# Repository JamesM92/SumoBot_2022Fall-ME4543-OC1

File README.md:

# SumoBot_2022Fall-ME4543-OC1
group design project sumobot for mechatronics

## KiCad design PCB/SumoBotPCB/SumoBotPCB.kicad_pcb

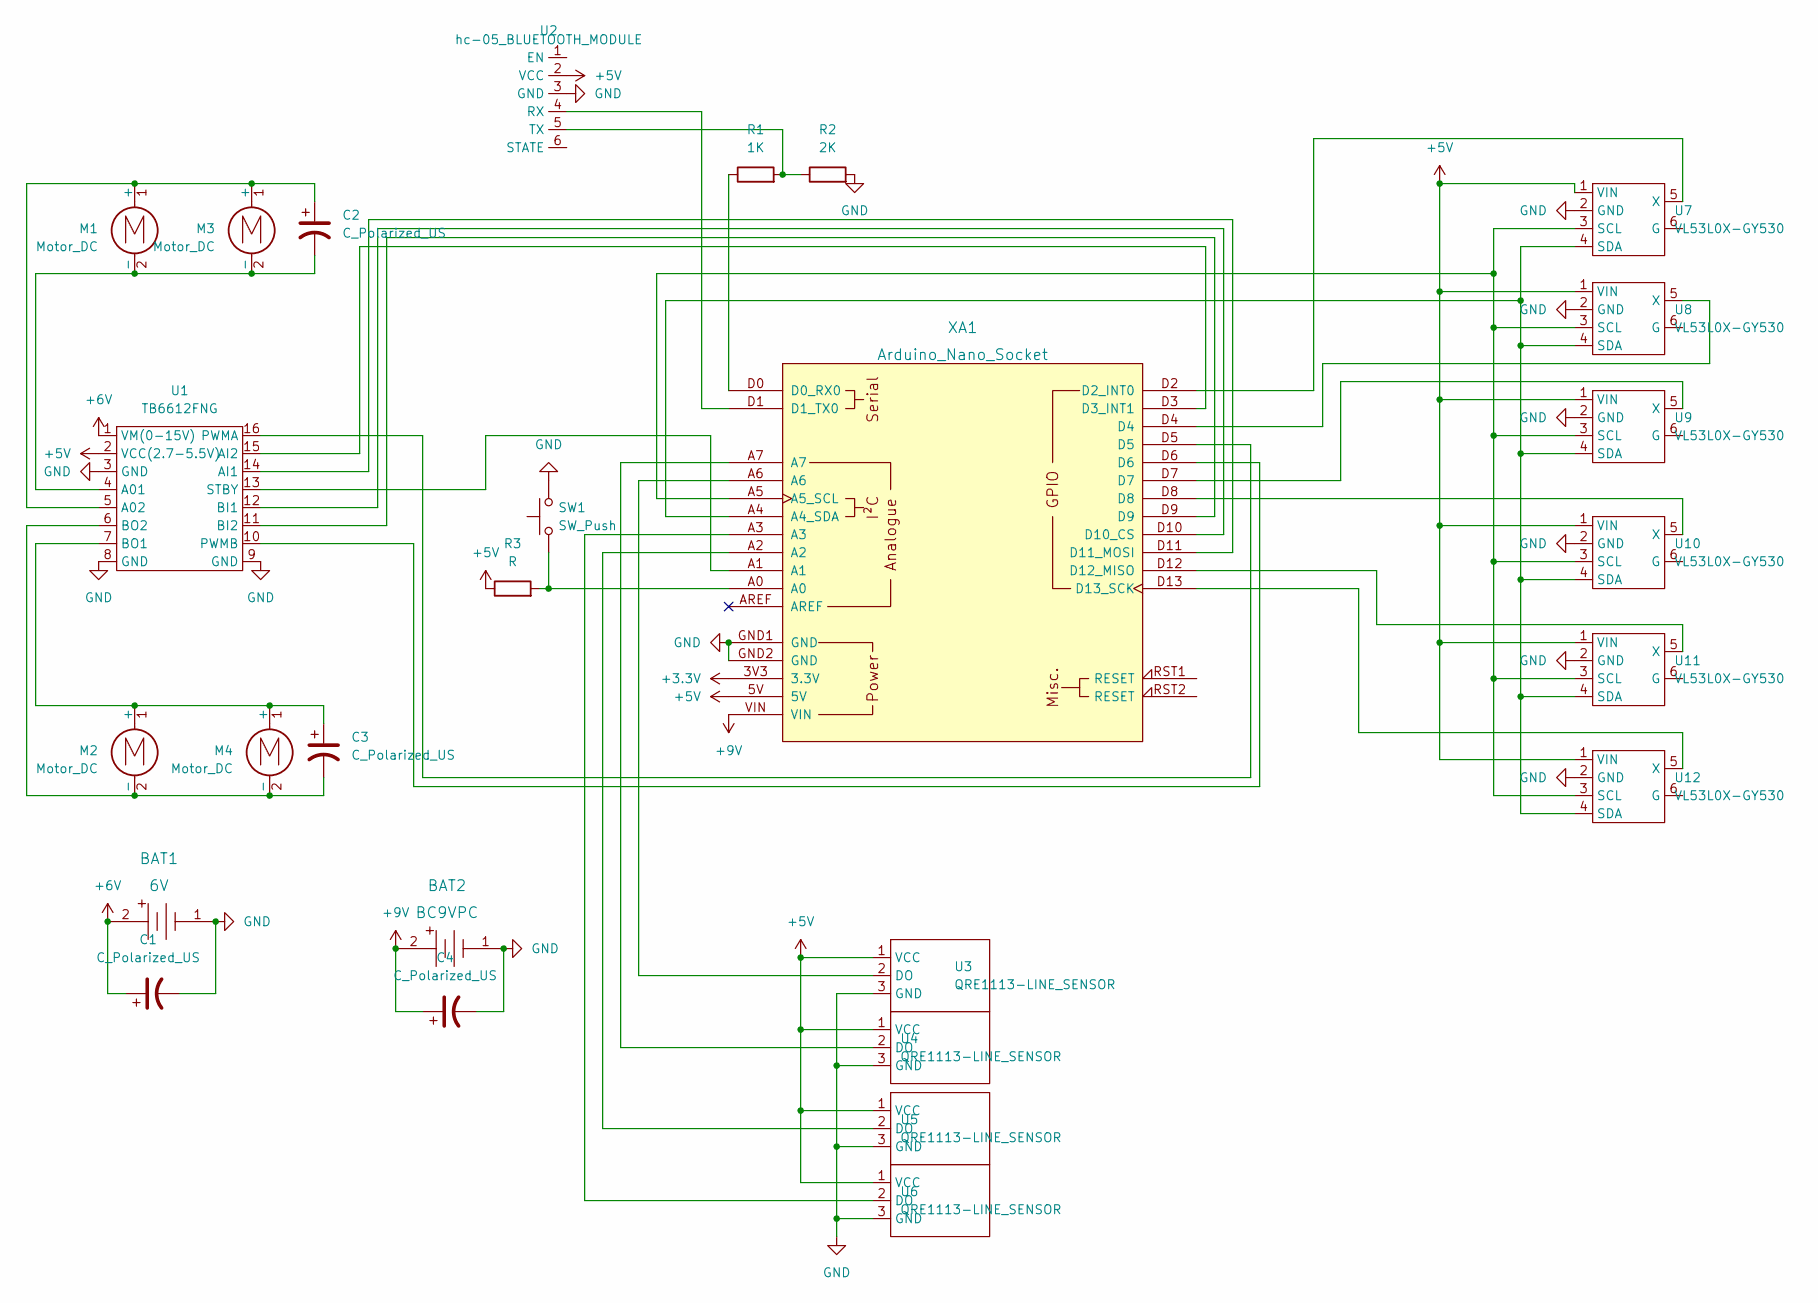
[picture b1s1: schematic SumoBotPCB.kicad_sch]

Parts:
BAT1: 6V; PinHeader_1x02_P2.54mm_Vertical; MPN BC9VPC; Digi-Key_PN BC9VPC-ND
BAT2: BC9VPC; PinHeader_1x02_P2.54mm_Vertical; MPN BC9VPC; Digi-Key_PN BC9VPC-ND
C1, C2, C3, C4: C_Polarized_US; CP_Radial_D8.0mm_P5.00mm
M1, M2, M3, M4: Motor_DC; PinHeader_1x02_P2.54mm_Vertical
R1: 1K; R_Axial_DIN0207_L6.3mm_D2.5mm_P2.54mm_Vertical
R2: 2K; R_Axial_DIN0207_L6.3mm_D2.5mm_P2.54mm_Vertical
R3: R; R_Axial_DIN0309_L9.0mm_D3.2mm_P5.08mm_Vertical
SW1: SW_Push; SW_PUSH_6mm_H4.3mm
U1: TB6612FNG; tb6612fng
U2: hc-05_BLUETOOTH_MODULE; PinHeader_1x06_P2.54mm_Vertical
U3, U4, U5, U6: QRE1113-LINE_SENSOR; PinHeader_1x03_P2.54mm_Vertical
U7, U8, U9, U10, U11, U12: VL53L0X-GY530
XA1: Arduino_Nano_Socket

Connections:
+3.3V: XA1.3V3 (3.3V)
+5V: R3.1, U1.2 (VCC(2.7-5.5V)), U2.2 (VCC), U3.1 (VCC), U4.1 (VCC), U5.1 (VCC), U6.1 (VCC), U7.1 (VIN), U8.1 (VIN), U9.1 (VIN), U10.1 (VIN), U11.1 (VIN), U12.1 (VIN), XA1.5V
+6V: BAT1.2, C1.1, U1.1 (VM(0-15V))
+9V: BAT2.2, C4.1, XA1.VIN
GND: BAT1.1, BAT2.1, C1.2, C4.2, R2.2, SW1.2, U1.3 (GND), U1.8 (GND), U1.9 (GND), U2.3 (GND), U3.3 (GND), U4.3 (GND), U5.3 (GND), U6.3 (GND), U7.2 (GND), U8.2 (GND), U9.2 (GND), U10.2 (GND), U11.2 (GND), U12.2 (GND), XA1.GND1 (GND), XA1.GND2 (GND)
unnamed: C2.1, M1.1 (+), M3.1 (+), U1.5 (A02)
unnamed: C2.2, M1.2 (-), M3.2 (-), U1.4 (A01)
unnamed: C3.1, M2.1 (+), M4.1 (+), U1.7 (BO1)
unnamed: C3.2, M2.2 (-), M4.2 (-), U1.6 (BO2)
unnamed: R1.1, XA1.D0 (D0_RX0)
unnamed: R1.2, R2.1, U2.5 (TX)
unnamed: U1.11 (BI2), XA1.D9
unnamed: U1.14 (AI1), XA1.D11 (D11_MOSI)
unnamed: U2.4 (RX), XA1.D1 (D1_TX0)
unnamed: U3.2 (DO), XA1.A6
unnamed: U4.2 (DO), XA1.A7
unnamed: U5.2 (DO), XA1.A2
unnamed: U6.2 (DO), XA1.A3
unnamed: U7.3 (SCL), U8.3 (SCL), U9.3 (SCL), U10.3 (SCL), U11.3 (SCL), U12.3 (SCL), XA1.A5 (A5_SCL)
unnamed: U7.4 (SDA), U8.4 (SDA), U9.4 (SDA), U10.4 (SDA), U11.4 (SDA), U12.4 (SDA), XA1.A4 (A4_SDA)
unnamed: U10.5 (X), XA1.D8
unnamed: U11.5 (X), XA1.D12 (D12_MISO)
unnamed: U12.5 (X), XA1.D13 (D13_SCK)
unnamed: R3.2, SW1.1, XA1.A0
unnamed: U1.13 (STBY), XA1.A1
unnamed: U7.5 (X), XA1.D2 (D2_INT0)
unnamed: U1.15 (AI2), XA1.D3 (D3_INT1)
unnamed: U8.5 (X), XA1.D4
unnamed: U1.16 (PWMA), XA1.D5
unnamed: U1.10 (PWMB), XA1.D6
unnamed: U9.5 (X), XA1.D7
unnamed: U1.12 (BI1), XA1.D10 (D10_CS)

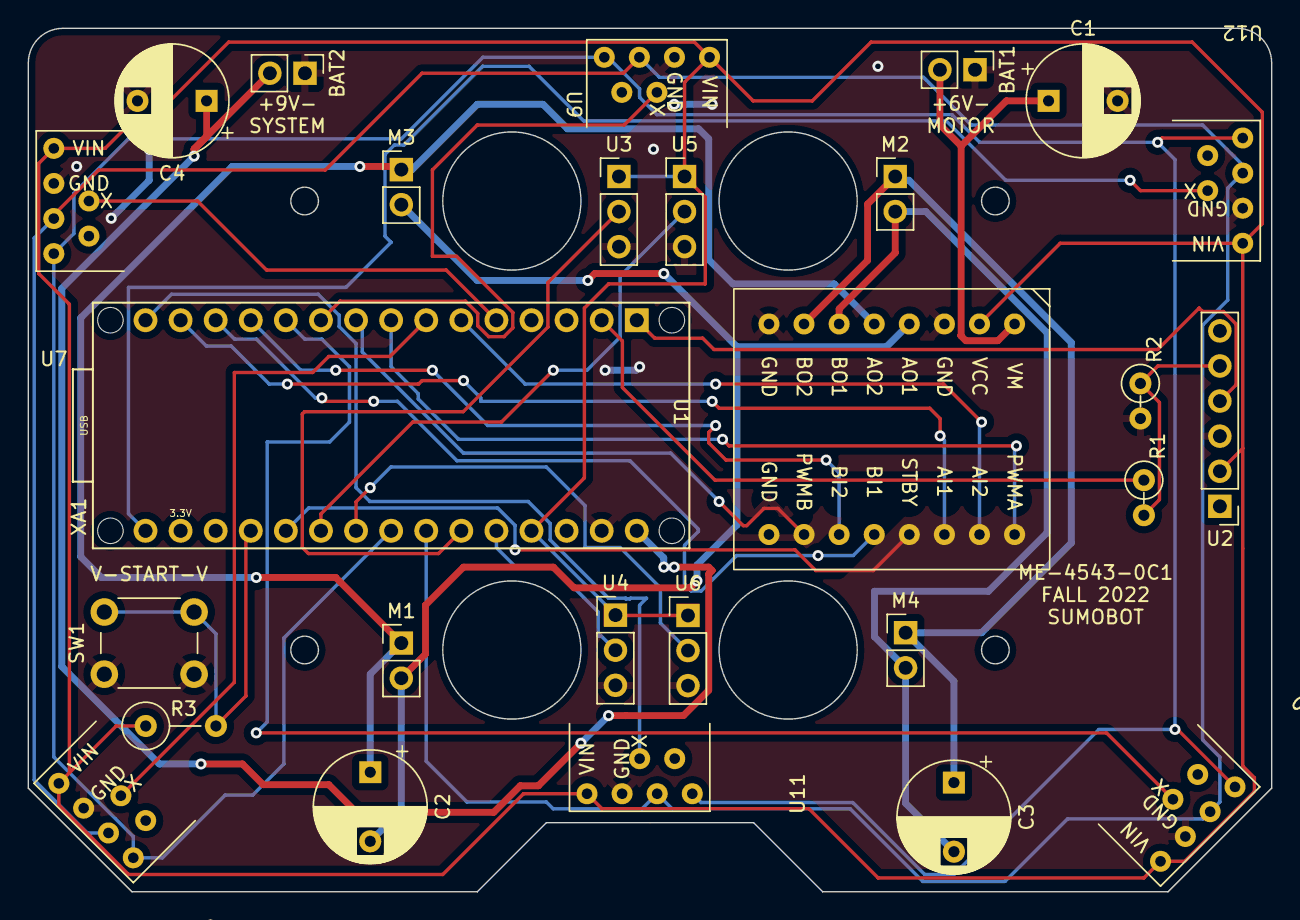
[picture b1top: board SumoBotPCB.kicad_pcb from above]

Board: 2 copper layers, 90.0 x 62.5 mm, 27 parts (0 on the bottom side), 31 nets.

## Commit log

2022-10-31 main commit of pcb files
2022-11-03 added example code
    added reference example code for project
2022-11-04 motor driver pwm
    correct pin assignment to have motor driver use 6 pwm pins to allow all options.
2022-11-04 added reference notes
    added excel notes from original designer
2022-11-04 ADDED STANDBY SWITCH
2022-11-04 re-assigned pins
    changed pin assignments on analog pins
2022-11-04 pwm groups change
    d5 and d6 pwm operate at a different frequency than the rest
2022-11-04 cleaned up schematic
2022-11-04 minor schemtic cleanup
2022-12-02 corrected driver foot print, add code
    corrected footpring of motor driver from being 0.5" to 0.6" and added the finalized code that works with arduino ide.
